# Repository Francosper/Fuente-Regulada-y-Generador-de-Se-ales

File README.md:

# Fuente Regulada - Generador de señales

## Descripción
Este proyecto consiste en el diseño y desarrollo de una fuente de tensión regulable que incorpora un generador de señales, pensado como una herramienta útil en laboratorios para proyectos de experimentación o entornos educativos. La fuente de alimentación está diseñada para ofrecer salidas de voltaje positivo y negativo, junto con una salida de tensión regulable según las necesidades que se requiera en una aplicación especifica. Además de su aplicación como fuente, el sistema incluye un generador de señales basado en el integrado XR2206CP el cual es un circuito integrado utilizado para la generación de distintos tipos de señales permitiendo generar señales senoidales, cuadradas y trignaulares. Su frecuencia de operación es configurable en un rango amplio que va desde 2 Hz hasta 1.3 MHz, lo que lo hace adecuado para una gran variedad de pruebas.
El generador de señales incorpora un mecanismo de ajuste tanto fino como grueso. Además, cuenta con un control de amplitud que permite al usuario variar la amplitud de las señales generadas según se quiera, la placa se presenta a continuación. 

<p align="center">
  
  <br>
  <em>Fig 1: Renderizado de la fuente regulada y generador de señales</em>
</p>

El artículo tiene como objetivo ofrecer una visión general de los componentes que componen el funcionamiento de la placa, abarcando sus principales características y especificaciones del sistema. Además, incluirá los archivos de software requeridos para su fabricacion, tales como los esquemas electrónicos, esquema de impresión de PCB, etc.

## Caracteristicas

A continuacion se nombran las caracteristicas de la placa 

| **Etapa**                     | **Descripción**                                           |
|------------------------------------|-----------------------------------------------------------|
| **Entrada de alimentación**        | Transformador de 20V eficaces                              |
| **Salidas de voltaje fijo**        | +12V y -12V                                               |
| **Salidas de voltaje regulable**   | 1.25V hasta 10V                                           |
| **Salidas de señales**             | Senoidal, cuadrada y triangular                           |
| **Variación de amplitud**          | Ajuste de amplitud de señales generadas (senoidales y triangulares) |
| **Variación de frecuencia**        | Ajuste fino y grueso de frecuencia con sus respectivas escalas |
| **Selector de señales**            | Switch para cambiar entre señal senoidal a triangular     |

- Escalas de frecuencia

Cada escala corresponde a las posiciones del selector de izquierda a derecha como se muestra a continuación
| **Escala** | **Rango**          |
|------------|--------------------|
| 1          | 2Hz – 220Hz        |
| 2          | 20Hz – 2.2KHz      |
| 3          | 450Hz – 50KHz      |
| 4          | 2KHz – 200KHz      |
| 5          | 25KHz – 1.3MHz     |

## Descripción general del hardware

Se detallan los componentes utilizados en el diseño, y se explica su funcionalidad dividida en módulos para facilitar la comprensión de cada parte del sistema.

- ### Fuente regulable +-12V

La implementación de la fuente consiste en un transformador reductor a 20 Volts eficaces. Mientras mayor sea la tensión eficaz de entrada peor es el rendimiento de la fuente, ya que esa tensión cae en los reguladores LM7812 y LM7912 aumentando la disipación de potencia teniendo la misma corriente de salida.

<p align="center">
  
  <br>
  <em>Fig. 2: Esquemático de fuente regulada +-12V.</em>
</p>

- ### Fuente regulable 2V – 10V

El circuito de la fuente regulable mostrado a continuación utiliza directamente la salida de 12V generada por el circuito anterior (Fig. 2). Este diseño incluye un potenciómetro de 2 kΩ para permitir la variación de tensión, complementado con capacitores de filtro.

<p align="center">
  
  <br>
  <em>Fig.3: Esquemático de fuente regulable 2V – 10V.</em>
</p>

- ### Generador de señales

Debajo de la imagen se describe el funcionamiento de cada uno de los bloques para un mejor entendimiento.

<p align="center">
  
  <br>
  <em>Fig.4: Esquemático del circuito generador de señales.</em>
</p>

| **Bloque** | **Descripción**                                                                                                                                   |
|------------|---------------------------------------------------------------------------------------------------------------------------------------------------|
| 1          | Alimentación: Toma los ±12V de la fuente regulable y cuenta con los filtros correspondientes para la reducción de ruido.                          |
| 2          | Control de amplitud: Afecta solamente la salida senoidal y triangular, permitiendo ajustar la amplitud de estas señales.                         |
| 3          | Control de frecuencia (parte resistiva): Modifica la resistencia del oscilador RC para variar la frecuencia de la señal de salida.                |
| 4          | Control de frecuencia (parte capacitiva): Modifica la capacidad del oscilador RC para variar la frecuencia de la señal de salida.                 |
| 5          | Selector de señales seno y triangular: Un switch que permite intercambiar entre señal senoidal y triangular en el pin de salida. Si el switch permanece cerrado se obtiene una señal senoidal, de otro modo, se tendrá una señal tipo triangular. |
| 6          | Salida de señales senoidal y triangular: Etapa de eliminación de continua, utilizando un operacional TL072 para aislar las señales y evitar la carga de la salida del XR2206. |
| 7          | Salida de señal cuadrada: Se toma desde un divisor resistivo y no tiene control de amplitud.                                                     |

## Fabricación del circuito

Se proporcionan los archivos necesarios para la fabricación de la placa, ya sea de manera casera, mediante el uso de una CNC, o para su envío a empresas de producción de circuitos profesionales. También se tendrá una tabla de los componentes necesarios.

Para descargar la carpeta con los archivos de KiCad visitar el siguiente link: [Carpeta de arcivos de KiCad](Archivos/Fuente)

A continuación, se muestran ambas caras de la placa.

<p align="center">
  
  <br>
  <em>Fig.5: Pistas para fabricación del PCB.</em>
</p>

<p align="center">
  
  <br>
  <em>Fig.6: Disposición de los componentes del sistema.</em>
</p>

Si se desea descargar los esquematicos mostrados, se encuentran a continuacion:

- [Pistas (Capa inferior)](Archivos/Fuente%20Generadora%201.0%20Cobre.pdf)
- [Componentes (capa superior)](Archivos/Fuente%20Generadora%201.0%20Frente.pdf)

Los componentes necesarios para la fabricacion son se ven en la siguiente tabla.

### Componentes

| Componente               | Nota                          | Valor         |
|--------------------------|-------------------------------|---------------|
| **J3**                    | Conector Phoenix 2 Pines      | -             |
| **J11**                   | Conector Phoenix 2 Pines      | -             |
| **J8**                    | Conector Phoenix 3 Pines      | -             |
| **J9**                    | Conector 3 Pines              | -             |
| **J1**                    | Conector 5 Pines              | -             |
| **J2**                    | Conector (1 pin o 5 pines)    | -             |
| **J5**                    | Conector 2 Pines              | -             |
| **J4, J6**                | Conector 3 Pines p/potenciómetro | 500kΩ       |
| **J7**                    | Conector 3 Pines p/potenciómetro | 10kΩ        |
| **J10**                   | Conector 3 Pines p/potenciómetro | 2kΩ         |
| **C2**                    | Capacitor cerámico            | 100pF         |
| **C3**                    | Capacitor cerámico            | 2,2nF         |
| **C4**                    | Capacitor cerámico            | 47nF          |
| **C5, C12, C14, C15, C17** | Capacitor cerámico            | 100nF         |
| **C10, C11**              | Capacitor cerámico            | 220nF         |
| **C1**                    | Capacitor electrolítico       | 100uF         |
| **C6, C18**               | Capacitor electrolítico       | 1uF           |
| **C7, C8**                | Capacitor electrolítico       | 4700uF        |
| **C9, C13, C16**          | Capacitor electrolítico       | 10uF          |
| **D1, D2, D3, D4**        | Diodo                         | 1N4001        |
| **U1**                    | Regulador lineal 12V          | LM7812        |
| **U2**                    | Regulador lineal -12V         | LM7912        |
| **U5**                    | Regulador lineal              | LM317         |
| **U4A**                   | Amplificador Operacional      | TL072         |
| **R1**                    | Resistencia                   | 1kΩ           |
| **R2**                    | Resistencia                   | 33kΩ          |
| **R3**                    | Resistencia                   | 330Ω          |
| **R4, R5, R6**            | Resistencia                   | 4,7kΩ         |
| **R7**                    | Resistencia                   | 100Ω          |
| **R8**                    | Resistencia                   | 240Ω          |
| **R9**                    | Resistencia                   | 680Ω          |
| **R10**                   | Resistencia                   | 10kΩ          |

Si se busca tener un entendimiento mas profundo de sistema, tales como las curvas de regulacion, respuesta en frecuencia y otros tipos de comportamientos, se recomienda leer la hoja de datos que se presenta a continuacion: [Hoja de datos](Archivos/Hoja_de_datos_Fuente_Regulable_y_generador.pdf)

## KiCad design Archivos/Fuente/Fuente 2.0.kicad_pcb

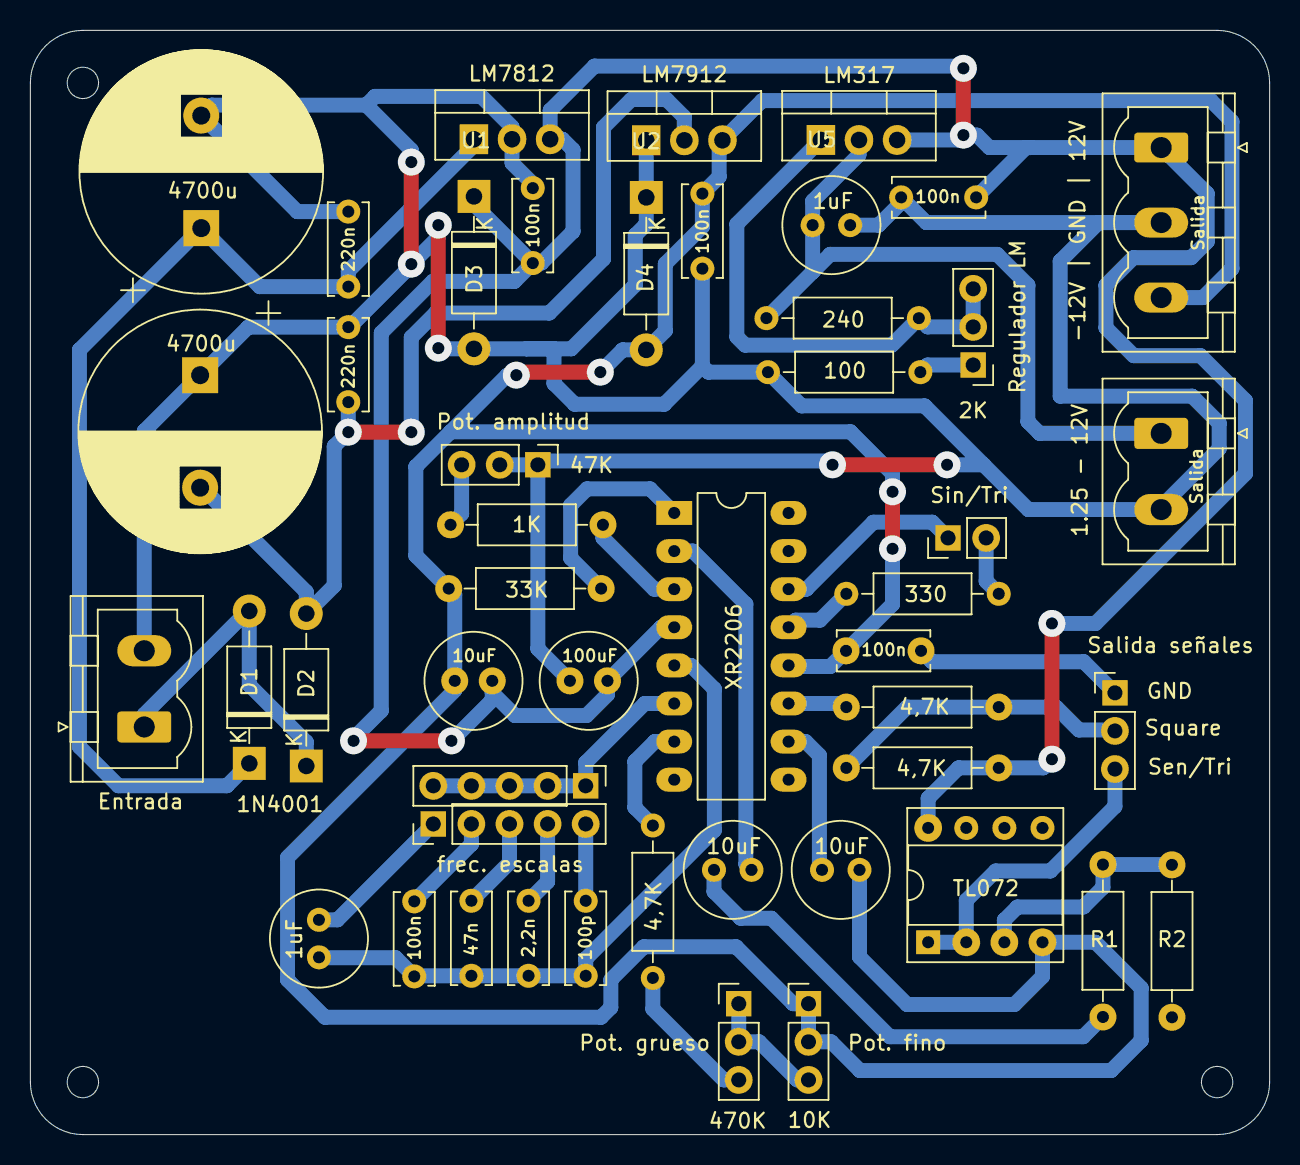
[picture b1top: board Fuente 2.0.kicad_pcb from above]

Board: 2 copper layers, 82.6 x 73.6 mm, 48 parts (0 on the bottom side), 32 nets.

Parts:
C1: 100uF; C_Radial_D6.3mm_H11.0mm_P2.50mm
C2: 100p; C_Disc_D6.0mm_W2.5mm_P5.00mm
C3: 2,2n; C_Disc_D6.0mm_W2.5mm_P5.00mm
C4: 47n; C_Disc_D6.0mm_W2.5mm_P5.00mm
C5, C12, C14, C15, C17: 100n; C_Disc_D6.0mm_W2.5mm_P5.00mm
C6, C18: 1uF; C_Radial_D6.3mm_H11.0mm_P2.50mm
C7, C8: 4700u; CP_Radial_D16.0mm_P7.50mm
C9, C13, C16: 10uF; C_Radial_D6.3mm_H11.0mm_P2.50mm
C10, C11: 220n; C_Disc_D6.0mm_W2.5mm_P5.00mm
D1, D2, D3, D4: 1N4001; D_DO-41_SOD81_P10.16mm_Horizontal
J1, J2: Conn_01x05; PinHeader_1x05_P2.54mm_Vertical
J3: IN; PhoenixContact_MSTBVA_2,5_2-G-5,08_1x02_P5.08mm_Vertical
J4: Amplitud 47K; PinHeader_1x03_P2.54mm_Vertical
J5: Sin/Tri; PinHeader_1x02_P2.54mm_Vertical
J6: 470K; PinHeader_1x03_P2.54mm_Vertical
J7: 10K; PinHeader_1x03_P2.54mm_Vertical
J8: Conn_01x03; PhoenixContact_MSTBVA_2,5_3-G_1x03_P5.00mm_Vertical
J9: OUTS; PinHeader_1x03_P2.54mm_Vertical
J10: Regulador 2K; PinHeader_1x03_P2.54mm_Vertical
J11: 1.25 - 12V; PhoenixContact_MSTBVA_2,5_2-G-5,08_1x02_P5.08mm_Vertical
R1: 1K; R_Axial_DIN0207_L6.3mm_D2.5mm_P10.16mm_Horizontal
R2: 33K; R_Axial_DIN0207_L6.3mm_D2.5mm_P10.16mm_Horizontal
R3: 330; R_Axial_DIN0207_L6.3mm_D2.5mm_P10.16mm_Horizontal
R4, R5, R6: 4,7K; R_Axial_DIN0207_L6.3mm_D2.5mm_P10.16mm_Horizontal
R7: 100; R_Axial_DIN0207_L6.3mm_D2.5mm_P10.16mm_Horizontal
R8: 240; R_Axial_DIN0207_L6.3mm_D2.5mm_P10.16mm_Horizontal
R9, R10: algo; R_Axial_DIN0207_L6.3mm_D2.5mm_P10.16mm_Horizontal
U1: LM7812; TO-220-3_Vertical
U2: LM7912; TO-220-3_Vertical
U3: XR2206; DIP-16_W7.62mm_LongPads
U4: TL072; DIP-8_W7.62mm_Socket
U5: LM317; TO-220-3_Vertical

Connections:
+5: C18.2, J11.1, R8.2, U5.2 (VO)
+12: C1.1, C9.1, C14.1, C17.1, D3.1 (K), J8.1, R5.2, U1.3 (VO), U3.4 (VCC), U4.8 (V+), U5.3 (VI)
-12: C9.2, C12.1, C13.2, C15.2, D4.2 (A), J7.1, J7.2, J8.3, R2.1, U2.3 (VO), U3.12 (GND), U4.4 (V-)
GND: C1.2, C7.2, C8.1, C10.2, C11.1, C12.2, C14.2, C15.1, C17.2, C18.1, D3.2 (A), D4.1 (K), J3.2, J4.1, J4.2, J8.2, J9.1, J11.2, R7.1, R9.2, U1.2 (GND), U2.1 (GND)
unnamed: C16.1, R10.1
unnamed: D1.2 (A), D2.1 (K), J3.1
unnamed: C7.1, C10.1, D1.1 (K), U1.1 (VI)
unnamed: C8.2, C11.2, D2.2 (A), U2.2 (VI)
unnamed: C6.1, J1.1
unnamed: C5.1, J1.2
unnamed: C4.1, J1.3
unnamed: C3.2, J1.4
unnamed: C2.1, J1.5
unnamed: J2.1, J2.2, J2.3, J2.4, J2.5, U3.6 (TC2)
unnamed: J4.3, R1.1
unnamed: J5.1, U3.14 (WAVEA2)
unnamed: J5.2, R3.1
unnamed: J6.1, J6.2, J7.3
unnamed: J6.3, R6.2
unnamed: J10.1, R7.2
unnamed: J10.2, J10.3, R8.1, U5.1 (ADJ)
unnamed: R2.2, U3.1 (AMSI)
unnamed: C13.1, U3.10 (BIAS)
unnamed: R1.2, U3.3 (MO)
unnamed: C16.2, U3.2 (STO)
unnamed: R4.1, U3.11 (SYNCO)
unnamed: C2.2, C3.1, C4.2, C5.2, C6.2, U3.5 (TC1)
unnamed: R6.1, U3.7 (TR1)
unnamed: R3.2, U3.13 (WAVEA1)
unnamed: R9.1, R10.2, U4.3 (+)
SQUARE OUT: J9.2, R4.2, R5.1
out sine tri: J9.3, U4.1, U4.2 (-)

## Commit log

2024-11-13 README.md
